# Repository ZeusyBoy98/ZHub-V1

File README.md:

# ZHub-V1
A basic USB hub built to suite my needs.
Made for Hack Club Fallout

## Zine

## What?
A basic USB hub with:
<ul>
<li> 1 Upstream USB-C
<li> 1 Downstream USB-C
<li> 3 Downstream USB-A
<li> USB 2.0 because I used a very basic chip
</ul>

## Why?
Because I don't have any USB-C USB hubs and A to C adapters are annoying. If I can just have one USB hub on me at all times, that can allow me to plug all the stuff I could possibly need in, then that achieves my goal.

## How?
In order to make this project for yourself, you'll need to purchase the board and get it assembled through PCBA with all the components below (PCB manufacturer-acceptable BOM at PCB/Gerbers/bom.csv). You'll also have to 3D print the case.
| Quantity | Item                 | URL                                                            | Unit Price ($USD) | Total Price ($USD)                |
| -------- | -------------------- | -------------------------------------------------------------- | ----------------- | --------------------------------- |
| 5        | CoreChips SL2.1A     | https://www.lcsc.com/product-detail/C192893.html?              | 0.2355            | 1.5920                            |
| 17       | USB A 2.0 Receptacle | https://www.lcsc.com/product-detail/C668591.html               | 0.0627            | 1.1288                            |
| 11       | USB C Receptacle     | https://www.lcsc.com/product-detail/C2765186.html              | 0.0633            | 0.7271                            |
| 60       | 1uf Capacitor        | https://www.lcsc.com/product-detail/C14445.html                | 0.0023            | 0.1380                            |
| 15       | 100nf Capacitor      | https://www.lcsc.com/product-detail/C1525.html?s_z=n_capacitor | 0.0013            | 0.0195                            |
| 30       | 5.1k Resistor        | https://www.lcsc.com/product-detail/C2906874.html              | 0.0006            | 0.0180                            |
| PCB      |                      |                                                                |                   | 3.10                              |
| PCBA     |                      |                                                                |                   | 30.78 (Includes component prices) |
| Shipping |                      |                                                                |                   | 9.24                              |
| Total    |                      |                                                                |                   | 43.12                             |

### Build Guide:

#### 1. Preparation<br>
Before starting, make sure you have:
<ul>
<li>The gerbers, pick and place files, and BOM, all available in this repository
<li>A 3D printer (or get the printed parts from someone else)
</ul>

#### 2. Ordering
Go to your PCB manufacturer of choice (Make sure they have PCBA) and follow their instructions on how to order.

#### 3. Case
3D print the print file, CAD/ZHub-V1-Print.3mf <br>
This has all the case parts you need (top and bottom)

#### 4. Assembly
Once the case has finished printing, place the assembled PCB into said case, then get the lid and slide it into the grooves of the bottom half of the case to close it.

#### 5. Profit
Plug a USB-C to C cable into the upstream port of the hub (the one not next to any other ports), and plug the other end of that cable into your computer. Then plug whatever USB devices into the downstream ports and...

This project does not need firmware, ignore the firmware folder.

Enjoy your ZHub!

## Renders

## Designing

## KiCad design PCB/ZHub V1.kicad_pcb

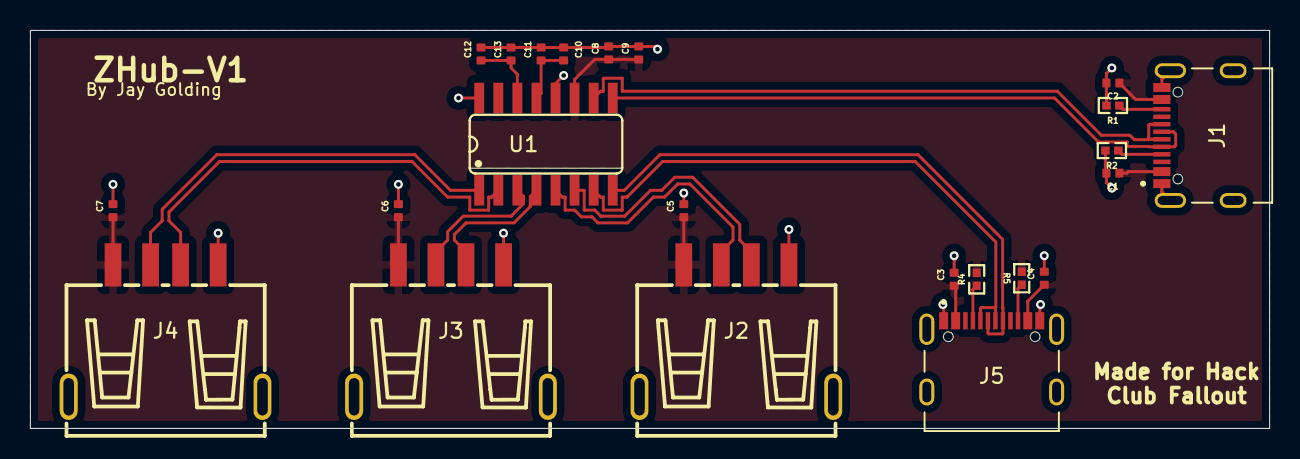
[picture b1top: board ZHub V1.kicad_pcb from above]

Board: 2 copper layers, 82.5 x 26.5 mm, 23 parts (0 on the bottom side), 18 nets.

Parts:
C1, C2, C3, C4, C5, C6, C7, C8, C10, C12: CAPC1005X55N; 1uf_0402
C9, C11, C13: CAPC1005X55N; 100nf_0402
J1, J5: TYPE-C_16PIN_2MD__073_; SHOUHAN_TYPE-C_16PIN_2MD__073_
J2, J3, J4: USB_A; USB-A-TH_10.0QHHTZB6.3
R1, R2, R3, R4: 5.1k_1210; R0402
U1: SL2.1A; SLA2.1s

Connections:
+5V: C1.1, C2.1, C3.1, C4.1, C5.1, C6.1, C7.1, C8.1, C9.1, J1.A4_B9 (VBUS_A), J1.B4_A9 (VBUS_B), J2.1 (VBUS), J3.1 (VBUS), J4.1 (VBUS), J5.A4_B9 (VBUS_A), J5.B4_A9 (VBUS_B), R3.2, R4.2, U1.11 (VDD5)
/DN: J1.A7 (DN1), J1.B7 (DN2), U1.9 (DM)
/DN1: J5.A7 (DN1), J5.B7 (DN2), U1.7 (DM1)
/DN2: J2.2 (D-), U1.5 (DM2)
/DN3: J3.2 (D-), U1.3 (DM3)
/DN4: J4.2 (D-), U1.1 (DM4)
/DP: J1.A6 (DP1), J1.B6 (DP2), U1.10 (DP)
/DP1: J5.A6 (DP1), J5.B6 (DP2), U1.8 (DP1)
/DP2: J2.3 (D+), U1.6 (DP2)
/DP3: J3.3 (D+), U1.4 (DP3)
/DP4: J4.3 (D+), U1.2 (DP4)
GND: C1.2, C2.2, C3.2, C4.2, C5.2, C6.2, C7.2, C8.2, C9.2, C10.2, C11.2, C12.2, C13.2, J1.A1_B12 (GND_A), J1.B1_A12 (GND_B), J1.SH1 (SHIELD), J1.SH2 (SHIELD), J1.SH3 (SHIELD), J1.SH4 (SHIELD), J2.4 (GND), J2.5 (Shield), J3.4 (GND), J3.5 (Shield), J4.4 (GND), J4.5 (Shield), J5.A1_B12 (GND_A), J5.B1_A12 (GND_B), J5.SH1 (SHIELD), J5.SH2 (SHIELD), J5.SH3 (SHIELD), J5.SH4 (SHIELD), R1.2, R2.2, U1.12 (GND), U1.16 (XIN)
unnamed: J1.A5 (CC1), R2.1
unnamed: J1.B5 (CC2), R1.1
unnamed: J5.A5 (CC1), R4.1
unnamed: J5.B5 (CC2), R3.1
unnamed: C12.1, C13.1, U1.14 (VDD18)
unnamed: C10.1, C11.1, U1.13 (VDD33)

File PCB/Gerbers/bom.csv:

Comment,Designator,Footprint,LCSC Part Number
100nf,"C9,C11,C13",100nf_0402,C1525
1uf,"C1,C2,C3,C4,C5,C6,C7,C8,C10,C12",1uf_0402,C14445
5.1k,"R1,R2,R3,R4",R0402,C2906874
SL2.1A,U1,SLA2.1S,C192893
USB A,"J2,J3,J4",USB-A-TH_10.0QHHTZB6.3,C668591
USB C,"J1,J5",SHOUHAN_TYPE-C_16PIN_2MD__073_,C2765186

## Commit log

2026-04-14 Finish shematic, PCB, and BOM
2026-04-15 Finished CAD
2026-04-17 Add proper README
2026-04-23 Add Zine
2026-04-23 Add F3D files
2026-04-23 Firmware disclaimer
2026-04-23 Firmware
2026-04-23 Remove unnecessary firmware folder
